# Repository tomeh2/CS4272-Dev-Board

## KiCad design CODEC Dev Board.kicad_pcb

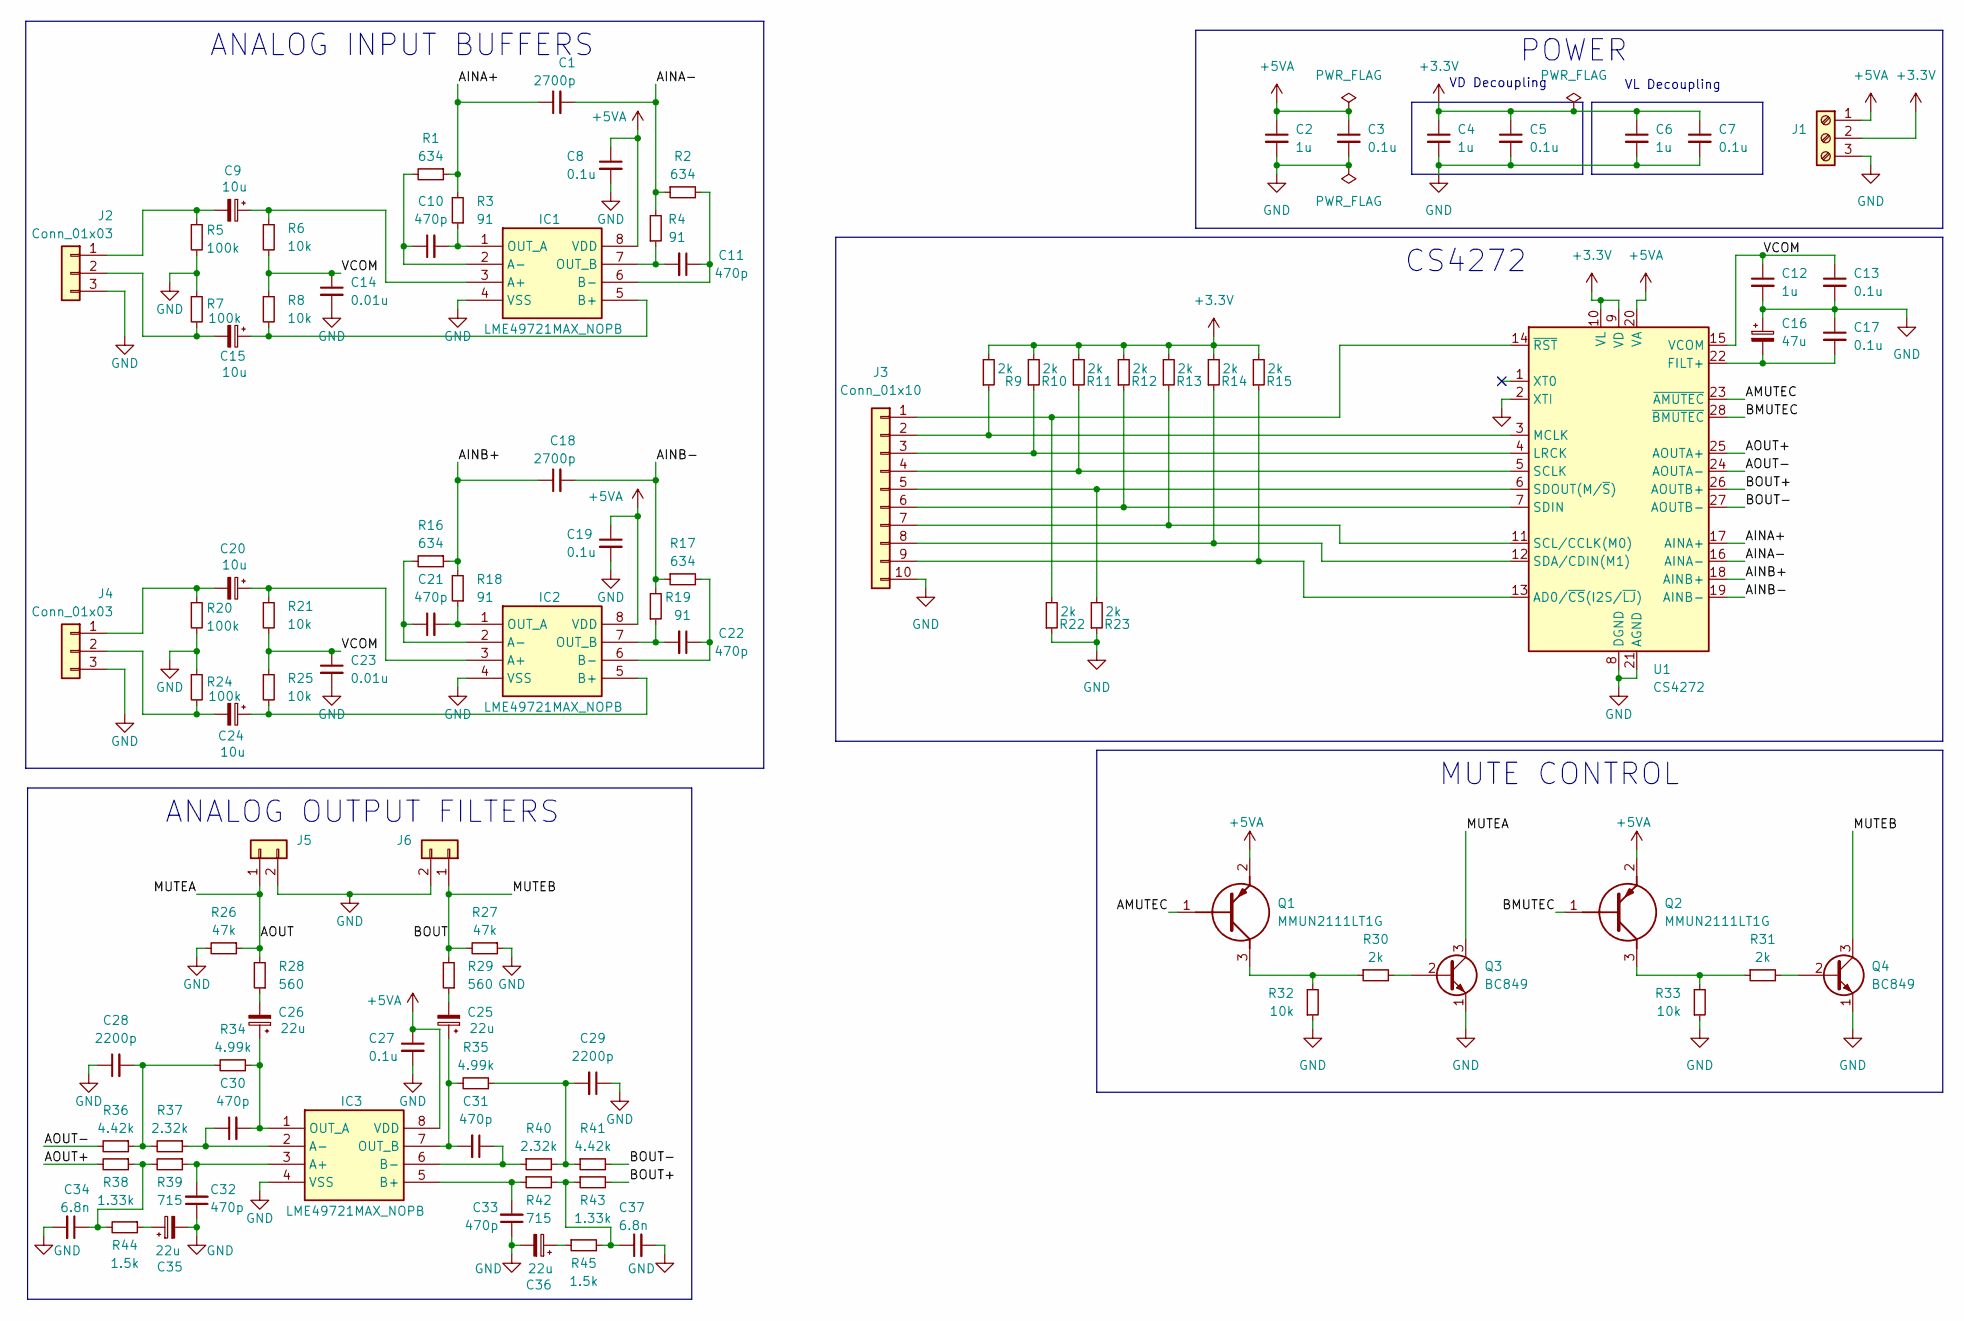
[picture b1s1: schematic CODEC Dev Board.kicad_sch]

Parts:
C1, C18: 2700p; C_0805_2012Metric_Pad1.18x1.45mm_HandSolder; Manufacturer_Part_Number C2012C0G1H272J060AA; Mouser Part Number 810-C2012C0G1H272J-1
C2, C4, C6, C12: 1u; C_0805_2012Metric_Pad1.18x1.45mm_HandSolder; Manufacturer_Part_Number C2012X7R1H105K125AB; Mouser Part Number 810-C2012X7R1H105K
C3, C5, C7, C8, C13, C17, C19, C27: 0.1u; C_0805_2012Metric_Pad1.18x1.45mm_HandSolder; Manufacturer_Part_Number C2012X7R1H104K085AA; Mouser Part Number 810-C2012X7R1H104K-2
C9, C15, C20, C24: 10u; CP_Radial_D8.0mm_P3.50mm; Manufacturer_Part_Number UVR2C100MPD; Mouser Part Number 647-UVR2C100MPD
C10, C11, C21, C22, C30, C31, C32, C33: 470p; C_0805_2012Metric_Pad1.18x1.45mm_HandSolder; Manufacturer_Part_Number C2012C0G2W471J060AA; Mouser Part Number 810-C2012C0G2W471JAA
C14, C23: 0.01u; C_0805_2012Metric_Pad1.18x1.45mm_HandSolder; Manufacturer_Part_Number C2012C0G1H103J060AA; Mouser Part Number 810-C2012C0G1H103J-1
C16: 47u; CP_Radial_D10.0mm_P5.00mm; Manufacturer_Part_Number UVR2A470MPD; Mouser Part Number 647-UVR2A470MPD
C25, C26, C35, C36: 22u; CP_Radial_D10.0mm_P5.00mm; Manufacturer_Part_Number UVR2D220MPD; Mouser Part Number 647-UVR2D220MPD
C28, C29: 2200p; C_0805_2012Metric_Pad1.18x1.45mm_HandSolder; Manufacturer_Part_Number C2012C0G1H222J085AA; Mouser Part Number 810-C2012C0G1H222J-2
C34, C37: 6.8n; C_0805_2012Metric_Pad1.18x1.45mm_HandSolder; Manufacturer_Part_Number C2012C0G1H682J060AA; Mouser Part Number 810-C2012C0G1H682J-1
IC1, IC2, IC3: LME49721MAX_NOPB; SOIC127P600X175-8N; Mouser Part Number 926-LME49721MAX/NOPB
J1: Screw_Terminal_01x03; TerminalBlock_Phoenix_PT-1,5-3-3.5-H_1x03_P3.50mm_Horizontal; Manufacturer_Part_Number 1984620; Mouser Part Number 651-1984620
J2, J4: Conn_01x03; PinHeader_1x03_P2.54mm_Vertical
J3: Conn_01x10; PinHeader_1x10_P2.54mm_Vertical
J5, J6: Conn_01x02; PinHeader_1x02_P2.54mm_Vertical
Q1, Q2: MMUN2111LT1G; SOT-23; Mouser Part Number 863-MMUN2111LT1G
Q3, Q4: BC849; SOT-23; Manufacturer_Part_Number BC849A; Mouser Part Number 637-BC849A
R1, R2, R16, R17: 634; R_0805_2012Metric_Pad1.20x1.40mm_HandSolder; Manufacturer_Part_Number ERJ-6ENF6340V; Mouser Part Number 667-ERJ-6ENF6340V
R3, R4, R18, R19: 91; R_0805_2012Metric_Pad1.20x1.40mm_HandSolder; Manufacturer_Part_Number ERJ-6ENF91R0V; Mouser Part Number 667-ERJ-6ENF91R0V
R5, R7, R20, R24: 100k; R_0805_2012Metric_Pad1.20x1.40mm_HandSolder; Manufacturer_Part_Number ERJ-6ENF1003V; Mouser Part Number 667-ERJ-6ENF1003V
R6, R8, R21, R25, R32, R33: 10k; R_0805_2012Metric_Pad1.20x1.40mm_HandSolder; Manufacturer_Part_Number ERJ-6ENF1002V; Mouser Part Number 667-ERJ-6ENF1002V
R9, R10, R11, R12, R13, R14, R15, R22, R23, R30, R31: 2k; R_0805_2012Metric_Pad1.20x1.40mm_HandSolder; Manufacturer_Part_Number ERJ-6ENF2001V; Mouser Part Number 667-ERJ-6ENF2001V
R26, R27: 47k; R_0805_2012Metric_Pad1.20x1.40mm_HandSolder; Manufacturer_Part_Number ERJ-6ENF4702V; Mouser Part Number 667-ERJ-6ENF4702V
R28, R29: 560; R_0805_2012Metric_Pad1.20x1.40mm_HandSolder; Manufacturer_Part_Number ERJ-6ENF5600V; Mouser Part Number 667-ERJ-6ENF5600V
R34, R35: 4.99k; R_0805_2012Metric_Pad1.20x1.40mm_HandSolder; Manufacturer_Part_Number ERJ-6ENF4991V; Mouser Part Number 667-ERJ-6ENF4991V
R36, R41: 4.42k; R_0805_2012Metric_Pad1.20x1.40mm_HandSolder; Manufacturer_Part_Number ERJ-6ENF4421V; Mouser Part Number 667-ERJ-6ENF4421V
R37, R40: 2.32k; R_0805_2012Metric_Pad1.20x1.40mm_HandSolder; Manufacturer_Part_Number ERJ-6ENF2321V; Mouser Part Number 667-ERJ-6ENF2321V
R38, R43: 1.33k; R_0805_2012Metric_Pad1.20x1.40mm_HandSolder; Manufacturer_Part_Number ERJ-6ENF1331V; Mouser Part Number 667-ERJ-6ENF1331V
R39, R42: 715; R_0805_2012Metric_Pad1.20x1.40mm_HandSolder; Manufacturer_Part_Number ERJ-6ENF7150V; Mouser Part Number 667-ERJ-6ENF7150V
R44, R45: 1.5k; R_0805_2012Metric_Pad1.20x1.40mm_HandSolder; Manufacturer_Part_Number ERJ-6ENF1501V; Mouser Part Number 667-ERJ-6ENF1501V
U1: CS4272; TSSOP-28_4.4x9.7mm_P0.65mm; Manufacturer_Part_Number CS4272K-CZZ; Mouser Part Number 777-CS4272-CZZ

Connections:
+3.3V: C4.1, C5.1, C6.1, C7.1, J1.2, R9.2, R10.2, R11.2, R12.2, R13.2, R14.2, R15.2, U1.9 (VD), U1.10 (VL)
+5VA: C2.1, C3.1, C8.1, C19.1, C27.1, IC1.8 (VDD), IC2.8 (VDD), IC3.8 (VDD), J1.1, Q1.2 (E), Q2.2 (E), U1.20 (VA)
/AINA+: C1.1, R1.1, R3.2, U1.17 (AINA+)
/AINA-: C1.2, R2.1, R4.2, U1.16 (AINA-)
/AINB+: C18.1, R16.1, R18.2, U1.18 (AINB+)
/AINB-: C18.2, R17.1, R19.2, U1.19 (AINB-)
/AMUTEC: Q1.1 (B), U1.23 (~AMUTEC)
/AOUT: J5.1, Q3.3 (C), R26.1, R28.2
/AOUT+: R38.2, U1.25 (AOUTA+)
/AOUT-: R36.2, U1.24 (AOUTA-)
/BMUTEC: Q2.1 (B), U1.28 (~BMUTEC)
/BOUT: J6.1, Q4.3 (C), R27.2, R29.2
/BOUT+: R43.2, U1.26 (AOUTB+)
/BOUT-: R41.2, U1.27 (AOUTB-)
/VCOM: C12.1, C13.1, C14.1, C23.1, R6.2, R8.1, R21.2, R25.1, U1.15 (VCOM)
GND: C2.2, C3.2, C4.2, C5.2, C6.2, C7.2, C8.2, C12.2, C13.2, C14.2, C16.1, C17.1, C19.2, C23.2, C27.2, C28.1, C29.1, C32.1, C33.1, C34.2, C35.2, C36.2, C37.2, IC1.4 (VSS), IC2.4 (VSS), IC3.4 (VSS), J1.3, J2.3, J3.10, J4.3, J5.2, J6.2, Q3.1 (E), Q4.1 (E), R5.2, R7.1, R20.2, R22.1, R23.1, R24.1, R26.2, R27.1, R32.1, R33.1, U1.2 (XTI), U1.8 (DGND), U1.21 (AGND)
unnamed: C25.2, R28.1
unnamed: C26.2, R29.1
unnamed: C28.2, R34.2, R36.1, R37.2
unnamed: C29.2, R35.1, R40.2, R41.1
unnamed: C34.1, R38.1, R39.2, R44.2
unnamed: C35.1, R44.1
unnamed: C36.1, R45.1
unnamed: C37.1, R42.2, R43.1, R45.2
unnamed: C9.1, IC1.3 (A+), R6.1
unnamed: C10.1, IC1.2 (A-), R1.2
unnamed: C15.1, IC1.5 (B+), R8.2
unnamed: C11.1, IC1.6 (B-), R2.2
unnamed: C10.2, IC1.1 (OUT_A), R3.1
unnamed: C11.2, IC1.7 (OUT_B), R4.1
unnamed: C20.1, IC2.3 (A+), R21.1
unnamed: C21.1, IC2.2 (A-), R16.2
unnamed: C24.1, IC2.5 (B+), R25.2
unnamed: C22.1, IC2.6 (B-), R17.2
unnamed: C21.2, IC2.1 (OUT_A), R18.1
unnamed: C22.2, IC2.7 (OUT_B), R19.1
unnamed: C32.2, IC3.3 (A+), R39.1
unnamed: C30.1, IC3.2 (A-), R37.1
unnamed: C33.2, IC3.5 (B+), R42.1
unnamed: C31.1, IC3.6 (B-), R40.1
unnamed: C25.1, C30.2, IC3.1 (OUT_A), R34.1
unnamed: C26.1, C31.2, IC3.7 (OUT_B), R35.2
unnamed: C9.2, J2.1, R5.1
unnamed: C15.2, J2.2, R7.2
unnamed: J3.1, R22.2, U1.14 (~RST)
unnamed: J3.2, R9.1, U1.3 (MCLK)
unnamed: J3.3, R10.1, U1.4 (LRCK)
unnamed: J3.4, R11.1, U1.5 (SCLK)
unnamed: J3.5, R23.2, U1.6 (SDOUT(M/~S))
unnamed: J3.6, R12.1, U1.7 (SDIN)
unnamed: J3.7, R13.1, U1.11 (SCL/CCLK(M0))
unnamed: J3.8, R14.1, U1.12 (SDA/CDIN(M1))
unnamed: J3.9, R15.1, U1.13 (AD0/~CS(I2S/~LJ))
unnamed: C20.2, J4.1, R20.1
unnamed: C24.2, J4.2, R24.2
unnamed: Q1.3 (C), R30.1, R32.2
unnamed: Q2.3 (C), R31.1, R33.2
unnamed: Q3.2 (B), R30.2
unnamed: Q4.2 (B), R31.2
unnamed: C16.2, C17.2, U1.22 (FILT+)

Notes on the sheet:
VD Decoupling
CS4272
ANALOG INPUT BUFFERS
POWER
VL Decoupling
MUTE CONTROL
ANALOG OUTPUT FILTERS

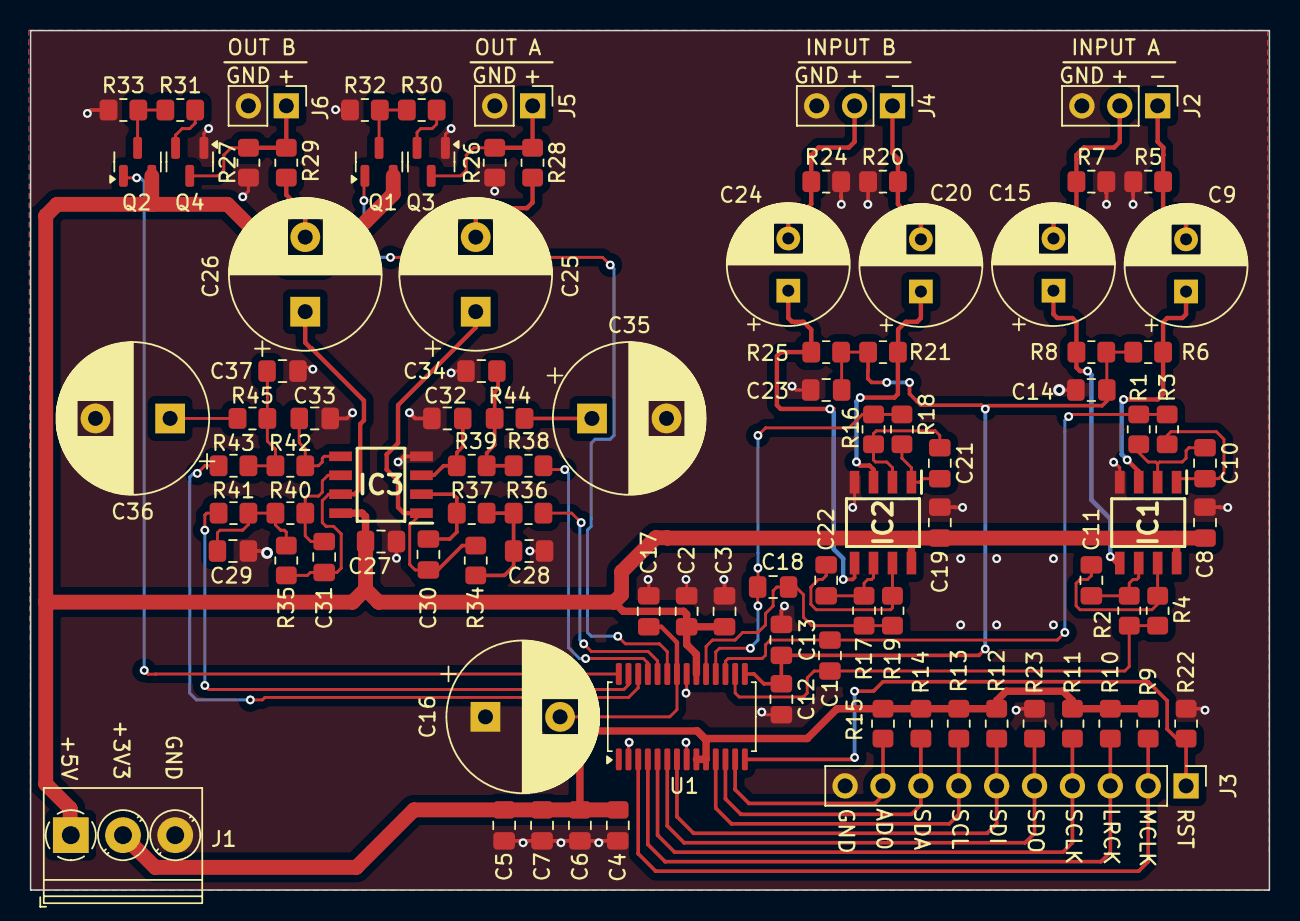
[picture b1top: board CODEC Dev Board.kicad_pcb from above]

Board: 2 copper layers, 83.1 x 57.6 mm, 96 parts (0 on the bottom side), 60 nets.

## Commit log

2024-09-01 First commit of a finished project
